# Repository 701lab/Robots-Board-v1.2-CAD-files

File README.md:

## What is Robots board v1.2?
 
**Robots board v1.2** is a cost affective board to implement small differential drive robots, for example, balancing robot. It uses _stm32g071cbu_ MCU, _DRV8848_ motor driver to control two small BDC motors, _ICM-20600_ 3-axis gyroscope and accelerometer, and _NRF24l01+_ as a radio module. Board support motors with incremental encoders and has a connector for UART communication.

## This repo contains
Autodesk Eagle CAD files for robots board v1.2 with schematics and PCB for a single board and PCB files for a pannel of 4 boards with 100x96mm (so it can be ordered as a pannel from chines manufacturers for a small price).

Open source **setup software for the board** can be found [here](https://github.com/701lab/rbv1.2-implementation).

### 3D model of the pannel of boards

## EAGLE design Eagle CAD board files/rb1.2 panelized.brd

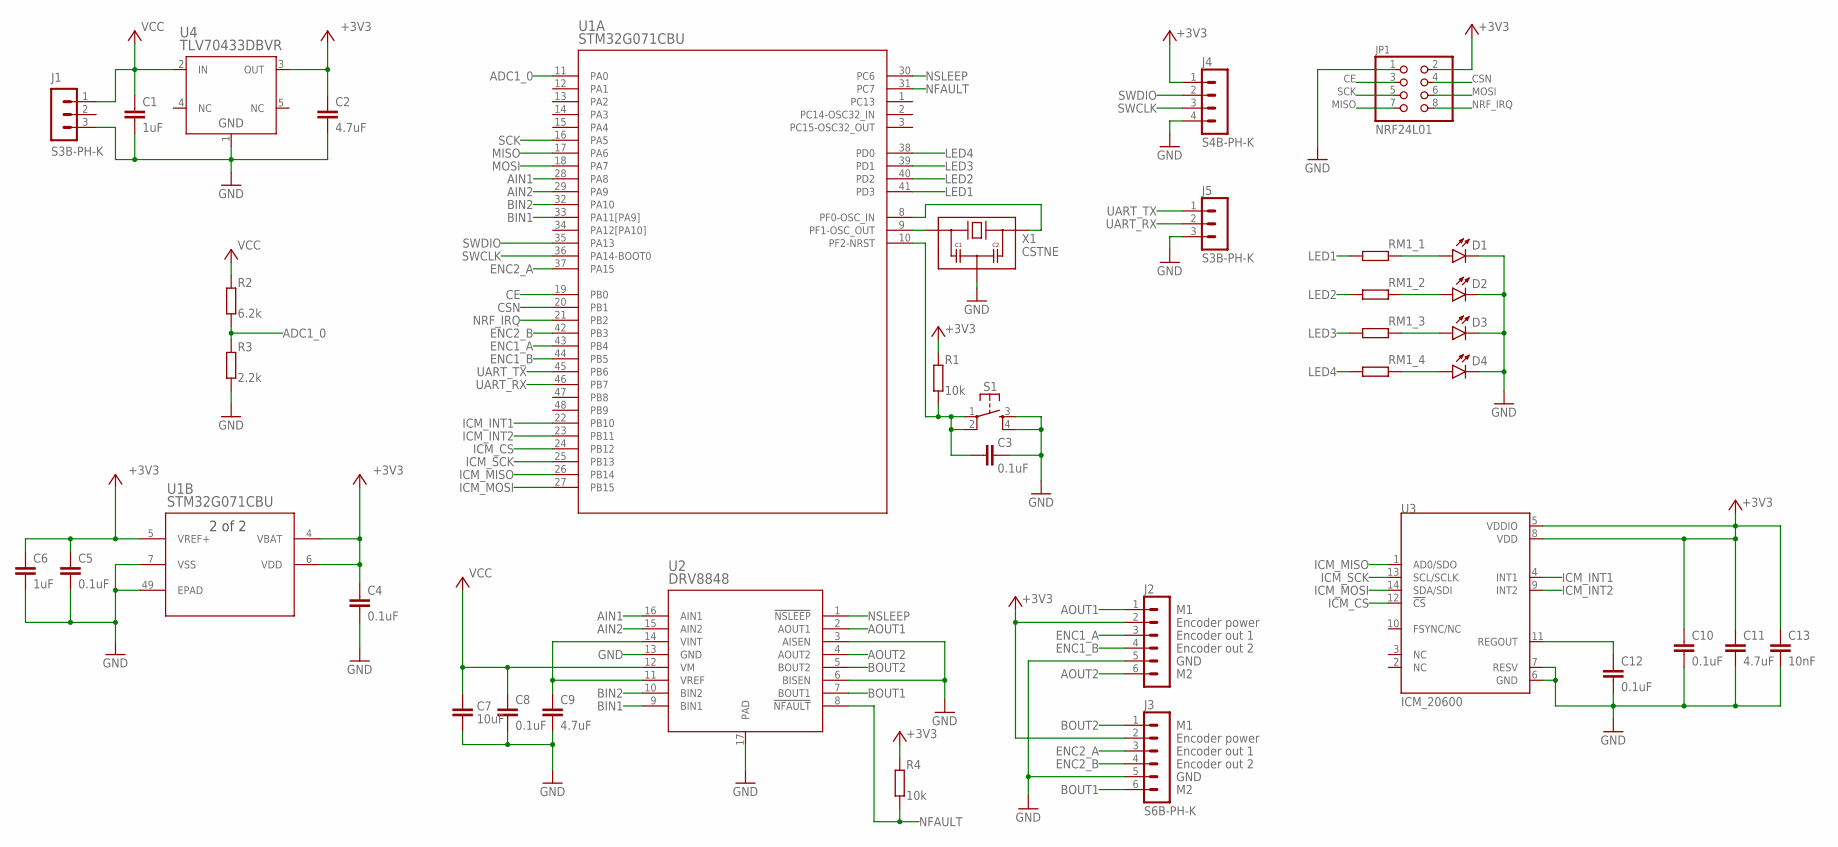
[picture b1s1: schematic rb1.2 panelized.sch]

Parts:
C1, C6: 1uF; C0603K
C2, C9, C11: 4.7uF; C0603K
C3: 0.1uF; C0402K
C4, C5, C8, C10, C12: 0.1uF; C0603K
C7: 10uF; C1206K
C13: 10nF; C0603K
D1, D2, D3, D4: LED0805; LED-0805
J1, J5: S3B-PH-K
J2, J3: S6B-PH-K
J4: S4B-PH-K
JP1: NRF24L01; 2X04
R1, R4: 10k; R0603
R2: 6.2k; R0603
R3: 2.2k; R0603
RM1: RES_ARRAY; 0603-ARC
S1: MOMENTARY-SWITCH-SPST-2-[SMD-5.2MM]; TACTILE_SWITCH_SMD_5.2MM
U1: STM32G071CBU; UFQFPN48-7X7MM
U2: DRV8848; HTSSOP
U3: ICM_20600; 14_PIN_LGA
U4: TLV70433DBVR; SOT-23-5
X1: CSTNE; MURATA_SMD_3P

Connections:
+3V3: C2.1, C4.1, C5.1, C6.1, C10.1, C11.1, C13.1, J2.2, J3.2, J4.1, JP1.2, R1.2, R4.2, U1.4 (VBAT), U1.5 (VREF+), U1.6 (VDD), U3.5 (VDDIO), U3.8 (VDD), U4.3 (OUT)
ADC1_0: R2.1, R3.2, U1.11 (PA0)
AIN1: U1.28 (PA8), U2.16 (AIN1)
AIN2: U1.29 (PA9), U2.15 (AIN2)
AOUT1: J2.1, U2.2 (AOUT1)
AOUT2: J2.6, U2.4 (AOUT2)
BIN1: U1.33 (PA11[PA9]), U2.9 (BIN1)
BIN2: U1.32 (PA10), U2.10 (BIN2)
BOUT1: J3.6, U2.7 (BOUT1)
BOUT2: J3.1, U2.5 (BOUT2)
CE: JP1.3, U1.19 (PB0)
CSN: JP1.4, U1.20 (PB1)
ENC1_A: J2.3, U1.43 (PB4)
ENC1_B: J2.4, U1.44 (PB5)
ENC2_A: J3.3, U1.37 (PA15)
ENC2_B: J3.4, U1.42 (PB3)
GND: C1.2, C2.2, C3.1, C4.2, C5.2, C6.2, C7.2, C8.2, C9.2, C10.2, C11.2, C12.2, C13.2, D1.- (C), D2.- (C), D3.- (C), D4.- (C), J1.3, J2.5, J3.5, J4.4, J5.3, JP1.1, R3.1, S1.3, S1.4, U1.7 (VSS), U1.49 (EPAD), U2.3 (AISEN), U2.6 (BISEN), U2.13 (GND), U2.17 (PAD), U3.6 (GND), U3.7 (RESV), U4.1 (GND), X1.2 (GND)
ICM_CS: U1.24 (PB12), U3.12 (!CS)
ICM_INT1: U1.22 (PB10), U3.4 (INT1)
ICM_INT2: U1.23 (PB11), U3.9 (INT2)
ICM_MISO: U1.26 (PB14), U3.1 (AD0/SDO)
ICM_MOSI: U1.27 (PB15), U3.14 (SDA/SDI)
ICM_SCK: U1.25 (PB13), U3.13 (SCL/SCLK)
LED1: RM1.1, U1.41 (PD3)
LED2: RM1.2 (1), U1.40 (PD2)
LED3: RM1.3 (1), U1.39 (PD1)
LED4: RM1.4 (1), U1.38 (PD0)
MISO: JP1.7, U1.17 (PA6)
MOSI: JP1.6, U1.18 (PA7)
unnamed: U1.8 (PF0-OSC_IN), X1.3 (OUT)
unnamed: U1.9 (PF1-OSC_OUT), X1.1 (IN)
unnamed: D4.+ (A), RM1.5 (2)
unnamed: D3.+ (A), RM1.6 (2)
unnamed: D2.+ (A), RM1.7 (2)
unnamed: D1.+ (A), RM1.8 (2)
NFAULT: R4.1, U1.31 (PC7), U2.8 (!NFAULT)
NRF_IRQ: JP1.8, U1.21 (PB2)
NSLEEP: U1.30 (PC6), U2.1 (!NSLEEP)
REG: C12.1, U3.11 (REGOUT)
RESET: C3.2, R1.1, S1.1, S1.2, U1.10 (PF2-NRST)
SCK: JP1.5, U1.16 (PA5)
SWCLK: J4.3, U1.36 (PA14-BOOT0)
SWDIO: J4.2, U1.35 (PA13)
UART_RX: J5.2, U1.46 (PB7)
UART_TX: J5.1, U1.45 (PB6)
VCC: C1.1, C7.1, C8.1, J1.1, R2.2, U2.12 (VM), U4.2 (IN)
VREF: C9.1, U2.11 (VREF), U2.14 (VINT)

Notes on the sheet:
GND
Encoder power
Encoder out 1
Encoder out 2

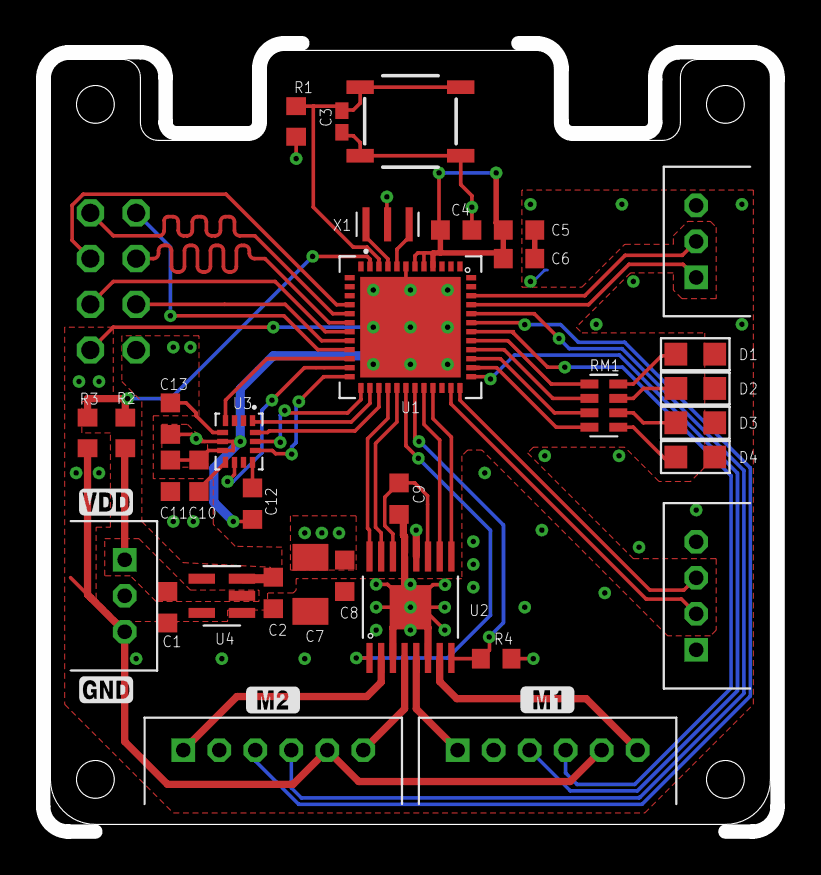
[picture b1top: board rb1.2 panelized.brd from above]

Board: 2 copper layers, 40.8 x 43.8 mm, 34 parts (1 on the bottom side), 47 nets.

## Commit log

2020-04-02 Initialization
2020-04-02 New readme
2020-04-02 Readme update

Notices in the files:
parts and their libraries:
con-jst-ph: Copyright (C) 2016, Bob Starr
